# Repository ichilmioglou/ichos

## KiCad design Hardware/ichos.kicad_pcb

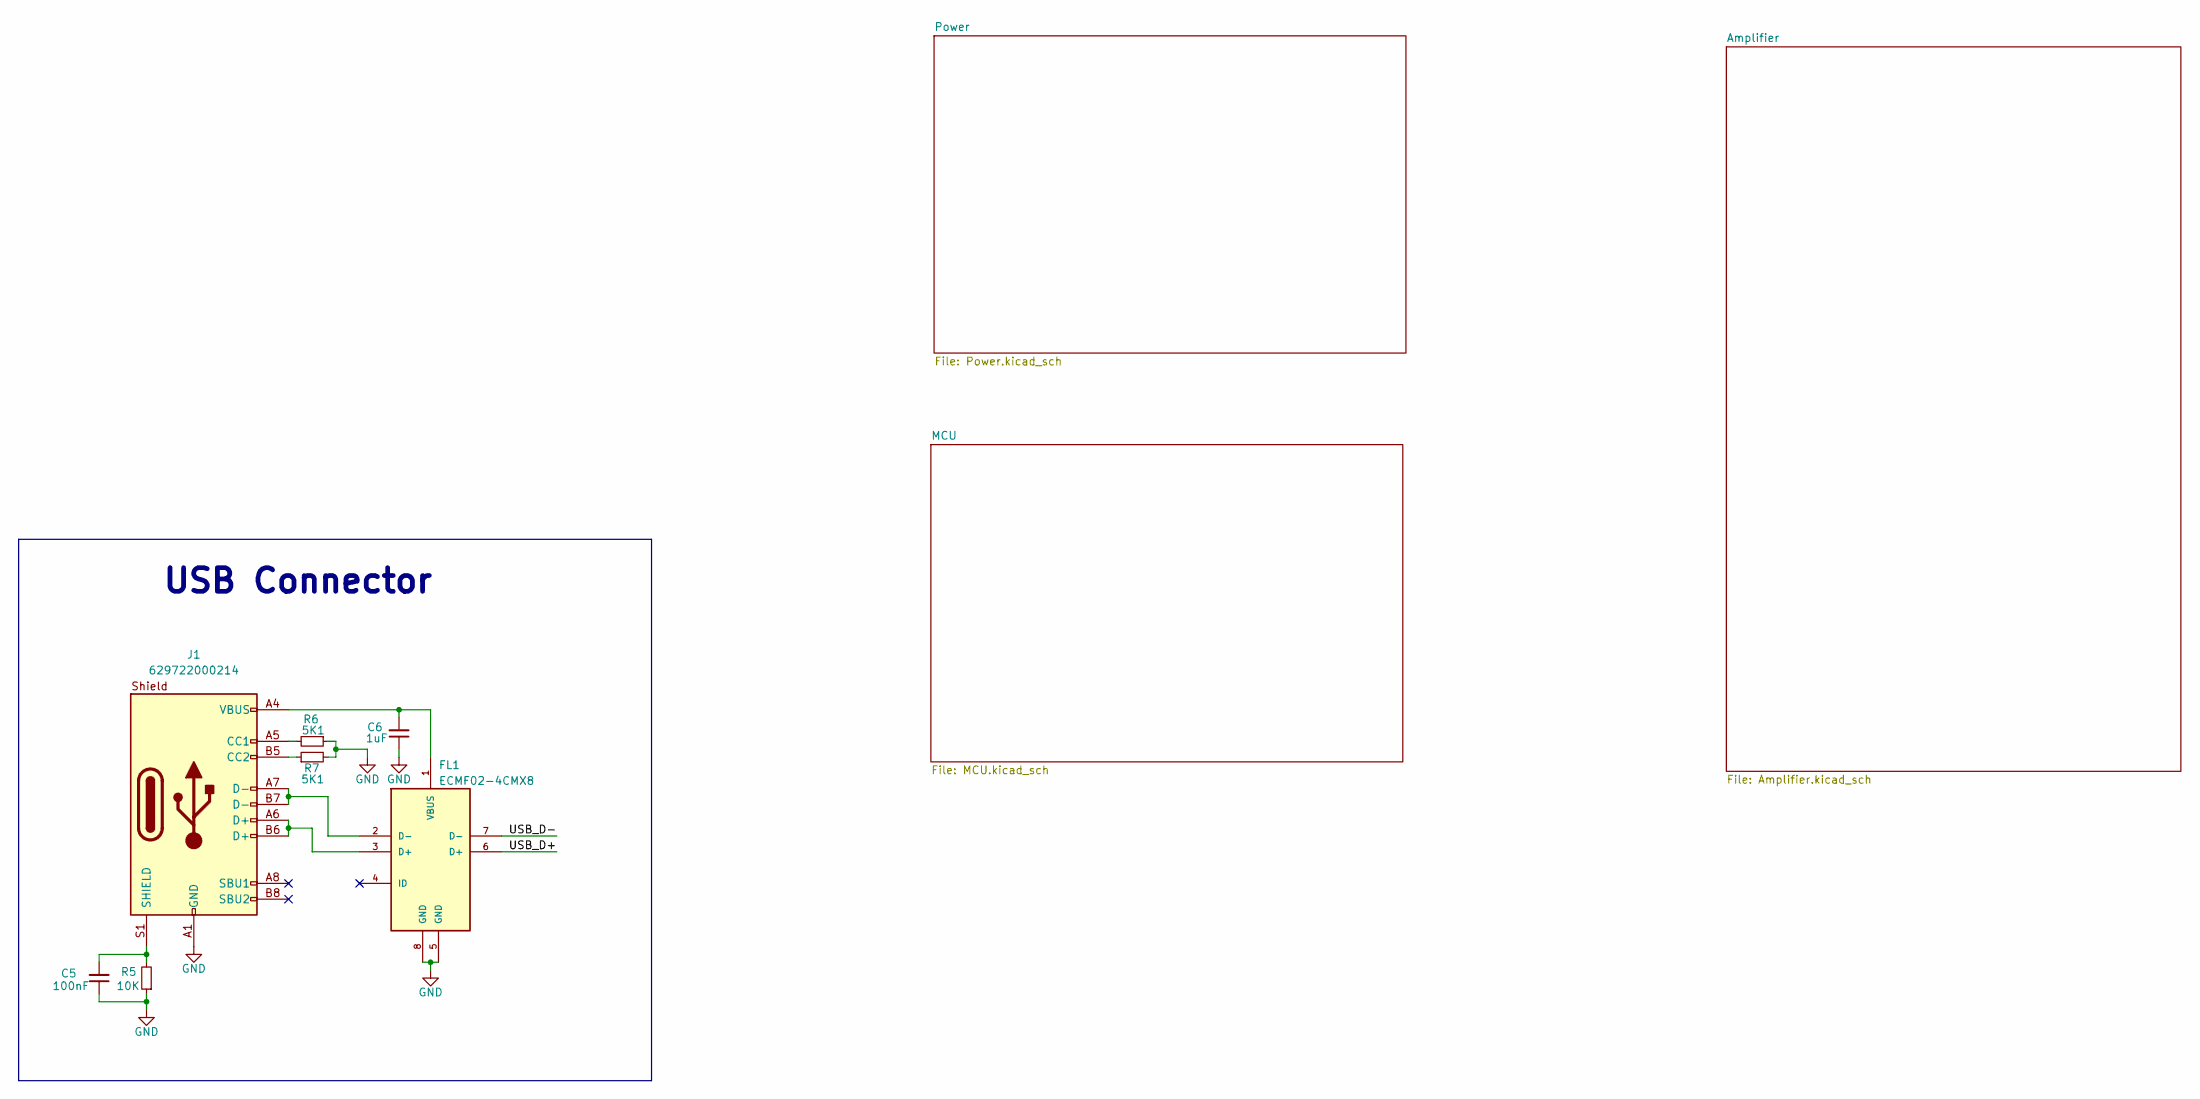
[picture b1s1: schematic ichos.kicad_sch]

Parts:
C5: 100nF; C_0402_1005Metric; Rating 50VDC 10% X7R
C6: 1uF; C_0603_1608Metric; Rating 50VDC 10% X7R
FL1: ECMF02-4CMX8
J1: 629722000214
R5: 10K; R_0402_1005Metric; Rating 1%
R6, R7: 5K1; R_0402_1005Metric; Rating 1%

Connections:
/USB_D+: FL1.6 (D+)
/USB_D-: FL1.7 (D-)
GND: C5.1, C6.1, FL1.5 (GND), FL1.8 (GND), J1.A1 (GND), J1.A12 (GND), J1.B1 (GND), J1.B12 (GND), R5.1, R6.1, R7.2; also elsewhere on the board
unnamed: FL1.3 (D+), J1.A6 (D+), J1.B6 (D+)
unnamed: FL1.2 (D-), J1.A7 (D-), J1.B7 (D-)
unnamed 26: C6.2, FL1.1 (VBUS), J1.A4 (VBUS), J1.A9 (VBUS), J1.B4 (VBUS), J1.B9 (VBUS); also elsewhere on the board
unnamed: J1.A5 (CC1), R6.2
unnamed: J1.B5 (CC2), R7.1
unnamed: C5.2, J1.S1 (SHIELD), R5.2

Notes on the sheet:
USB Connector

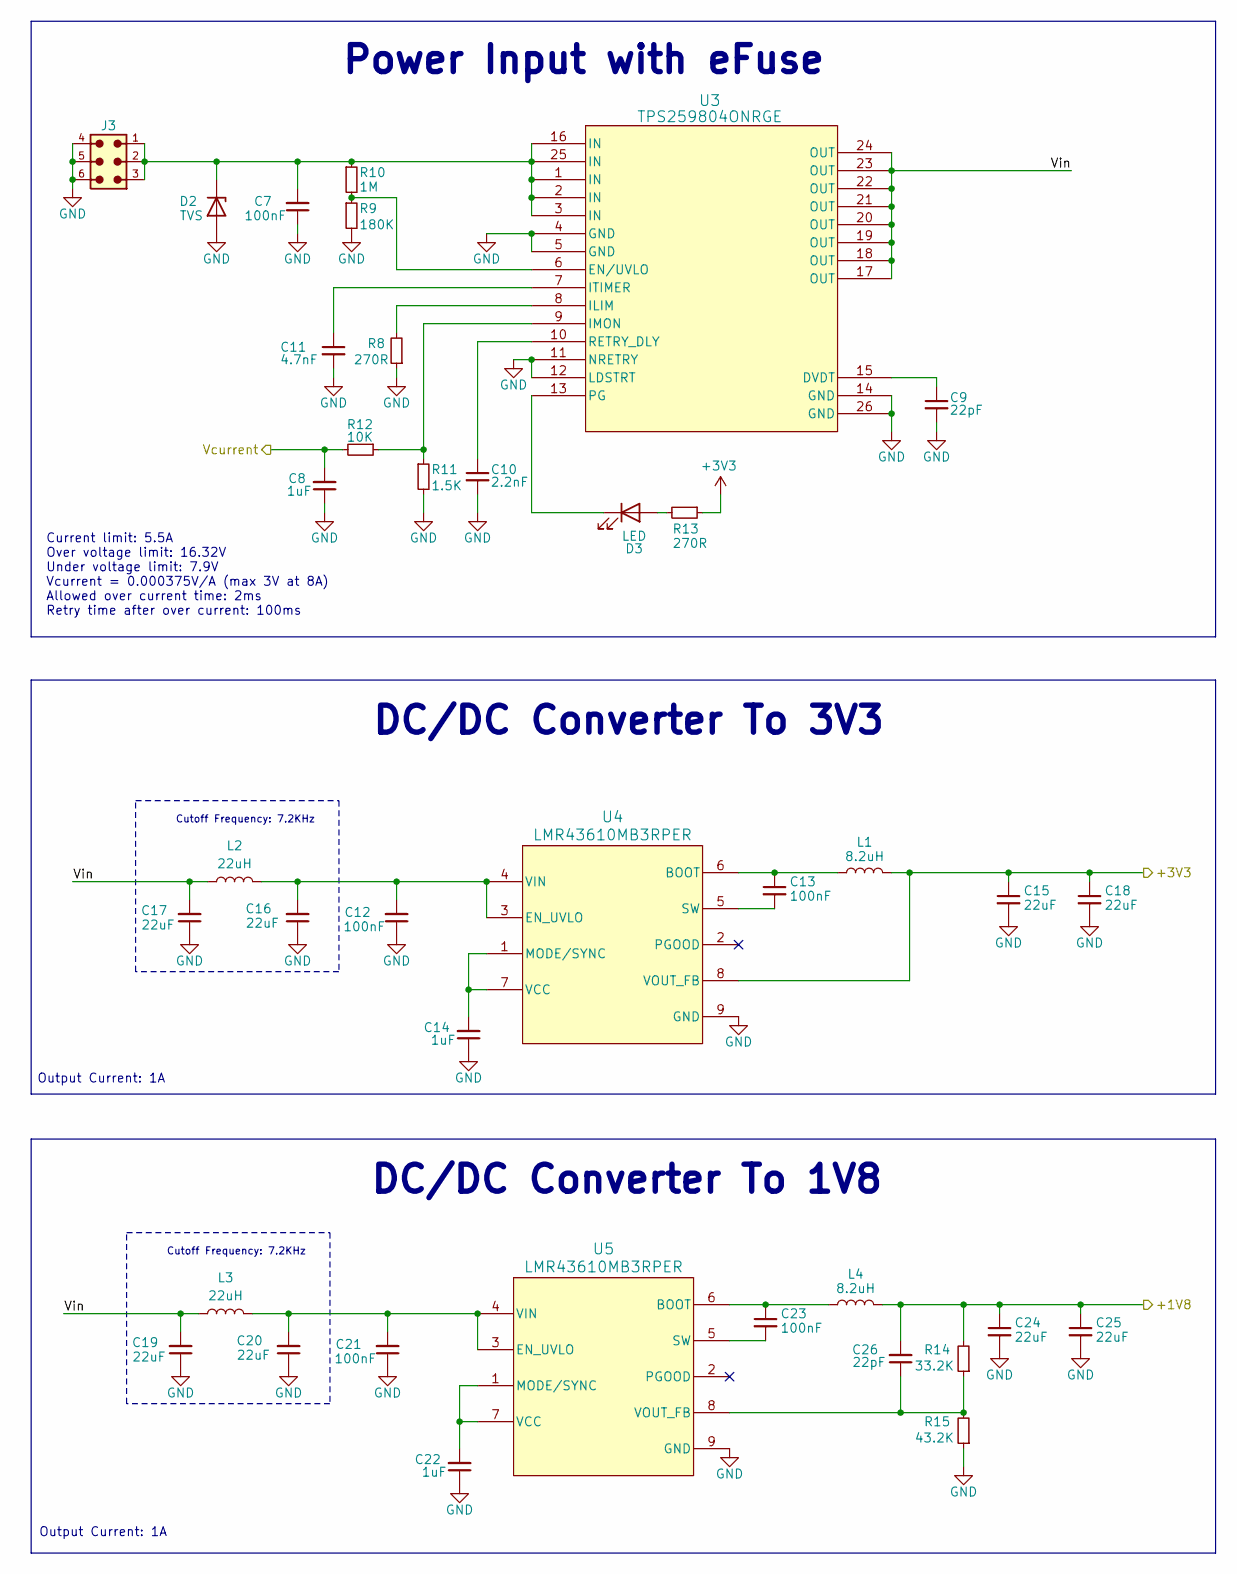
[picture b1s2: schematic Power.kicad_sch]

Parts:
C7, C12, C13, C21, C23: 100nF; C_0402_1005Metric; Rating 50VDC 10% X7R
C8, C14, C22: 1uF; C_0603_1608Metric; Rating 50VDC 10% X7R
C9, C26: 22pF; C_0402_1005Metric; Rating 100V 2% C0G
C10: 2.2nF; C_0402_1005Metric; Rating 50V 10% X7R
C11: 4.7nF; C_0402_1005Metric; Rating 50V 5% X7R
C15, C16, C17, C18, C19, C20, C24, C25: 22uF; C_1206_3216Metric; Rating 25VDC 10% X7R
D2: 824550121; D_SMC
D3: LED; LED_0603_1608Metric
J3: 64900621122
L1, L4: 8.2uH; 744042008
L2, L3: 22uH; 744053220
R8, R13: 270R; R_0402_1005Metric; Rating 1%
R9: 180K; R_0402_1005Metric; Rating 1%
R10: 1M; R_0402_1005Metric; Rating 1%
R11: 1.5K; R_0402_1005Metric; Rating 1%
R12: 10K; R_0402_1005Metric; Rating 1%
R14: 33.2K; R_0402_1005Metric; Rating 1%
R15: 43.2K; R_0402_1005Metric; Rating 1%
U3: TPS259804ONRGE; TPS259804ONRGER
U4, U5: LMR43610MB3RPER

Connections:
+1V8: C24.1, C25.1, C26.2, L4.2, R14.2; also elsewhere on the board
+3V3: C15.1, C18.1, L1.2, R13.1, U4.8 (VOUT_FB)
/Power/Vcurrent: C8.2, R12.2
/Power/Vin: C17.2, C19.2, L2.1, L3.1, U3.17 (OUT), U3.18 (OUT), U3.19 (OUT), U3.20 (OUT), U3.21 (OUT), U3.22 (OUT), U3.23 (OUT), U3.24 (OUT)
GND: C7.1, C8.1, C9.2, C10.2, C11.2, C12.1, C14.1, C15.2, C16.1, C17.1, C18.2, C19.1, C20.1, C21.1, C22.1, C24.2, C25.2, D2.2 (A), J3.4, J3.5, J3.6, R8.1, R9.2, R11.2, R15.1, U3.4 (GND), U3.5 (GND), U3.11 (NRETRY), U3.12 (LDSTRT), U3.14 (GND), U3.26 (GND), U4.9 (GND), U5.9 (GND); also elsewhere on the board
unnamed 21: C7.2, D2.1 (K), J3.1, J3.2, J3.3, R10.1, U3.1 (IN), U3.2 (IN), U3.3 (IN), U3.16 (IN), U3.25 (IN); also elsewhere on the board
unnamed: D3.2 (A), R13.2
unnamed: D3.1 (K), U3.13 (PG)
unnamed: C9.1, U3.15 (DVDT)
unnamed: R9.1, R10.2, U3.6 (EN/UVLO)
unnamed: R8.2, U3.8 (ILIM)
unnamed: R11.1, R12.1, U3.9 (IMON)
unnamed: C11.1, U3.7 (ITIMER)
unnamed: C10.1, U3.10 (RETRY_DLY)
unnamed: C13.1, L1.1, U4.6 (BOOT)
unnamed: C12.2, C16.2, L2.2, U4.3 (EN_UVLO), U4.4 (VIN)
unnamed: C14.2, U4.1 (MODE/SYNC), U4.7 (VCC)
unnamed: C13.2, U4.5 (SW)
unnamed: C23.1, L4.1, U5.6 (BOOT)
unnamed: C20.2, C21.2, L3.2, U5.3 (EN_UVLO), U5.4 (VIN)
unnamed: C22.2, U5.1 (MODE/SYNC), U5.7 (VCC)
unnamed: C23.2, U5.5 (SW)
unnamed: C26.1, R14.1, R15.2, U5.8 (VOUT_FB)

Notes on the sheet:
Cutoff Frequency: 7.2KHz
DC/DC Converter To 3V3
Output Current: 1A
DC/DC Converter To 1V8
Current limit: 5.5A Over voltage limit: 16.32V Under voltage limit: 7.9V Vcurrent = 0.000375V/A (max 3V at 8A) Allowed over current time: 2ms Retry time after over current: 100ms
Power Input with eFuse

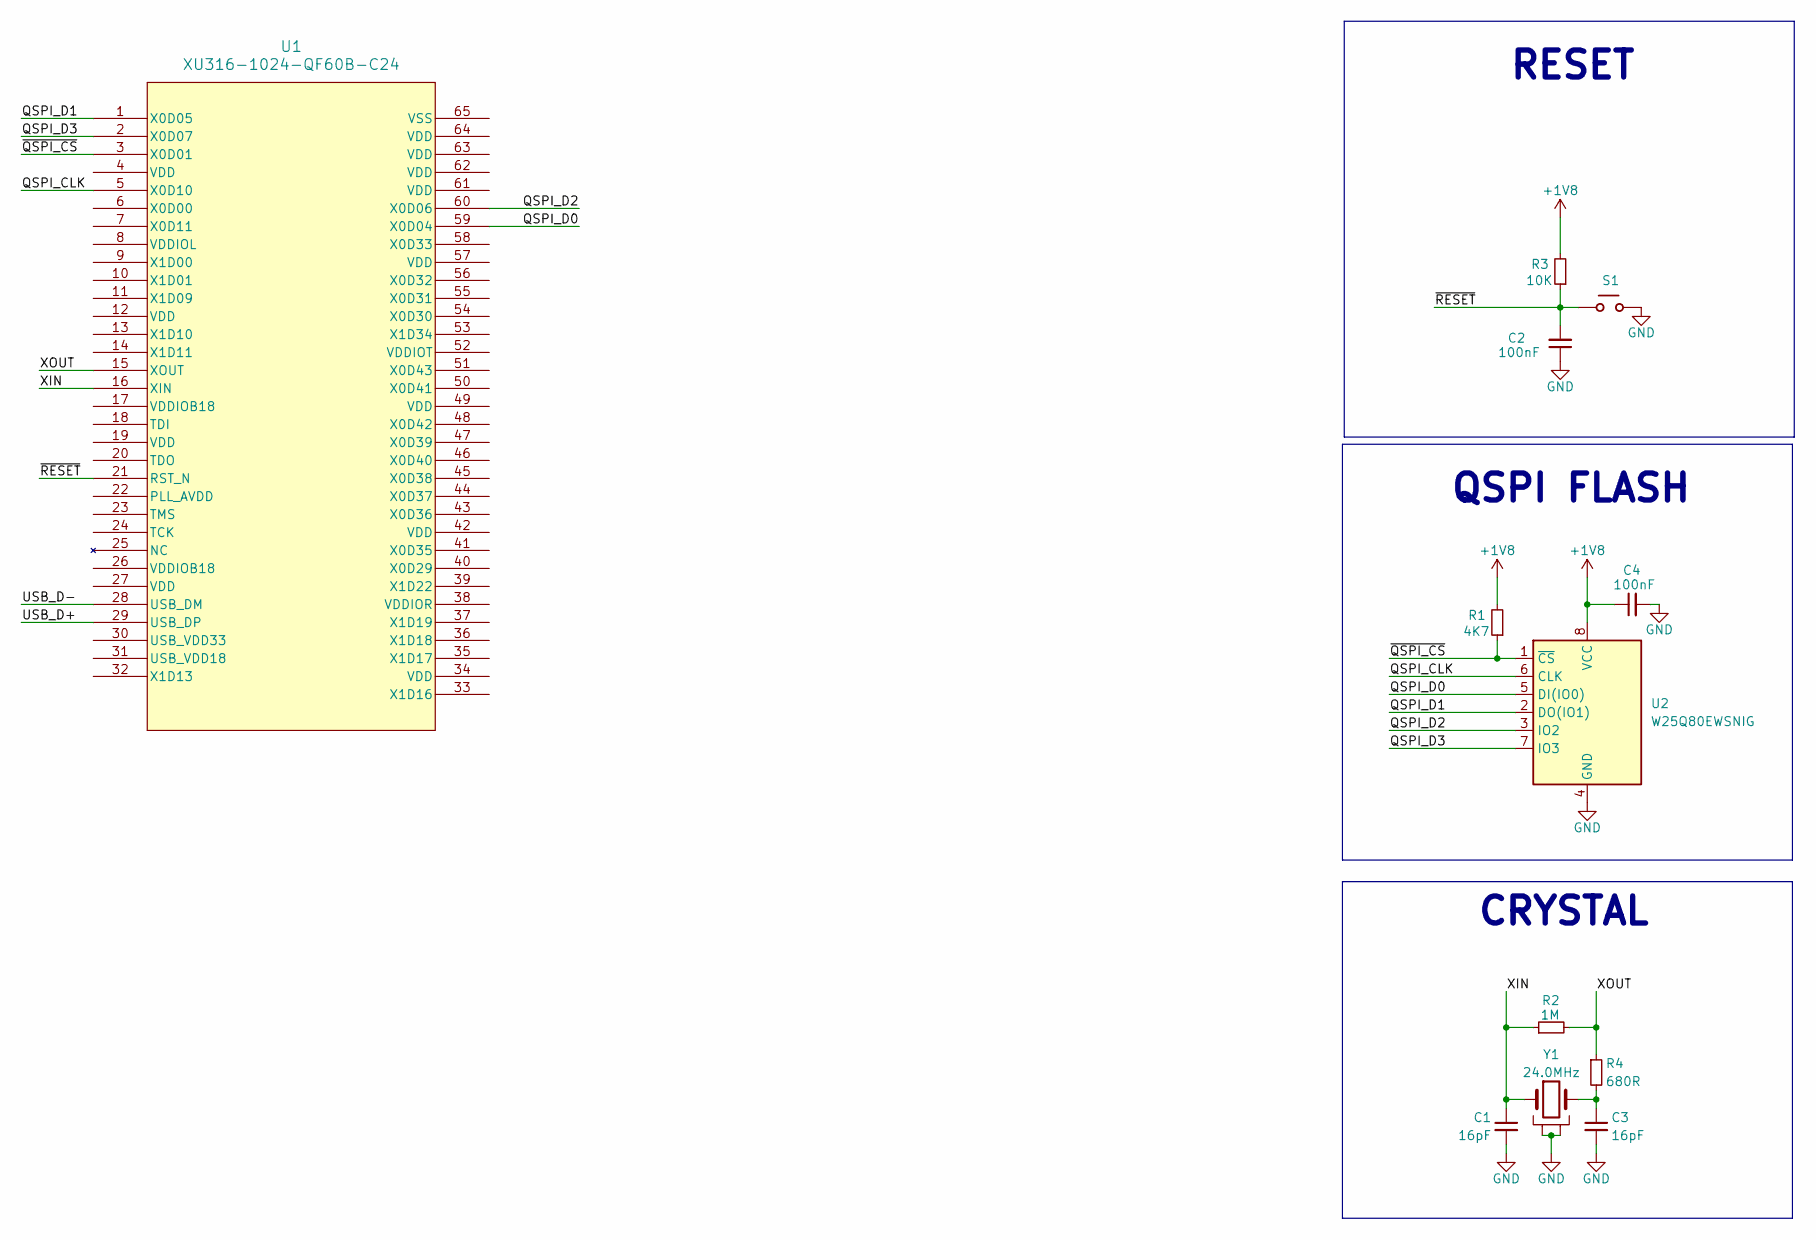
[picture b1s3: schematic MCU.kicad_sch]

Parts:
C1, C3: 16pF; C_0402_1005Metric; Rating 50VDC 1% C0G
C2, C4: 100nF; C_0402_1005Metric; Rating 50VDC 10% X7R
R1: 4K7; R_0402_1005Metric; Rating 1%
R2: 1M; R_0402_1005Metric; Rating 1%
R3: 10K; R_0402_1005Metric; Rating 1%
R4: 680R; R_0402_1005Metric; Rating 1%
S1: 430481031816
U1: XU316-1024-QF60B-C24; XU316-1024-QF60B-C32
U2: W25Q80EWSNIG; SOIC-8_5.23x5.23mm_P1.27mm
Y1: 24.0MHz; 830108340709

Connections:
+1V8: C4.1, R1.2, R3.2, U2.8 (VCC); also elsewhere on the board
/MCU/QSPI_CLK: U1.5 (X0D10), U2.6 (CLK)
/MCU/QSPI_D0: U1.59 (X0D04), U2.5 (DI(IO0))
/MCU/QSPI_D1: U1.1 (X0D05), U2.2 (DO(IO1))
/MCU/QSPI_D2: U1.60 (X0D06), U2.3 (IO2)
/MCU/QSPI_D3: U1.2 (X0D07), U2.7 (IO3)
/MCU/USB_D+: U1.29 (USB_DP)
/MCU/USB_D-: U1.28 (USB_DM)
/MCU/XIN: C1.1, R2.1, U1.16 (XIN), Y1.1
/MCU/XOUT: R2.2, R4.1, U1.15 (XOUT)
/MCU/~QSPI_CS: R1.1, U1.3 (X0D01), U2.1 (~CS)
/MCU/~RESET: C2.2, R3.1, S1.1, S1.2, U1.21 (RST_N)
GND: C1.2, C2.1, C3.2, C4.2, S1.3, S1.4, U2.4 (GND), Y1.2, Y1.3; also elsewhere on the board
unnamed: C3.1, R4.2, Y1.4

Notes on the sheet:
QSPI FLASH
RESET
CRYSTAL

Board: 2 copper layers, 60 parts (0 on the bottom side), 40 nets, no tracks yet.

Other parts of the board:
D1: SKM14; D_SOD-123F
F1: 0ZCG0035FF2C; Fuse_1812_4532Metric
J2: 691317510002

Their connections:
GND: J2.2; also elsewhere on the board
unnamed: D1.2 (A), F1.2
unnamed 21: J2.1; also elsewhere on the board
unnamed 26: F1.1; also elsewhere on the board

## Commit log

2024-10-04 hello world
2024-10-07 power
